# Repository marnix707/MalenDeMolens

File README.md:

# MalenDeMolens
Sensor om bedrijfstoestand van oude poldermolens te bepalen en door te sturen over het LoRaWAN netwerk.

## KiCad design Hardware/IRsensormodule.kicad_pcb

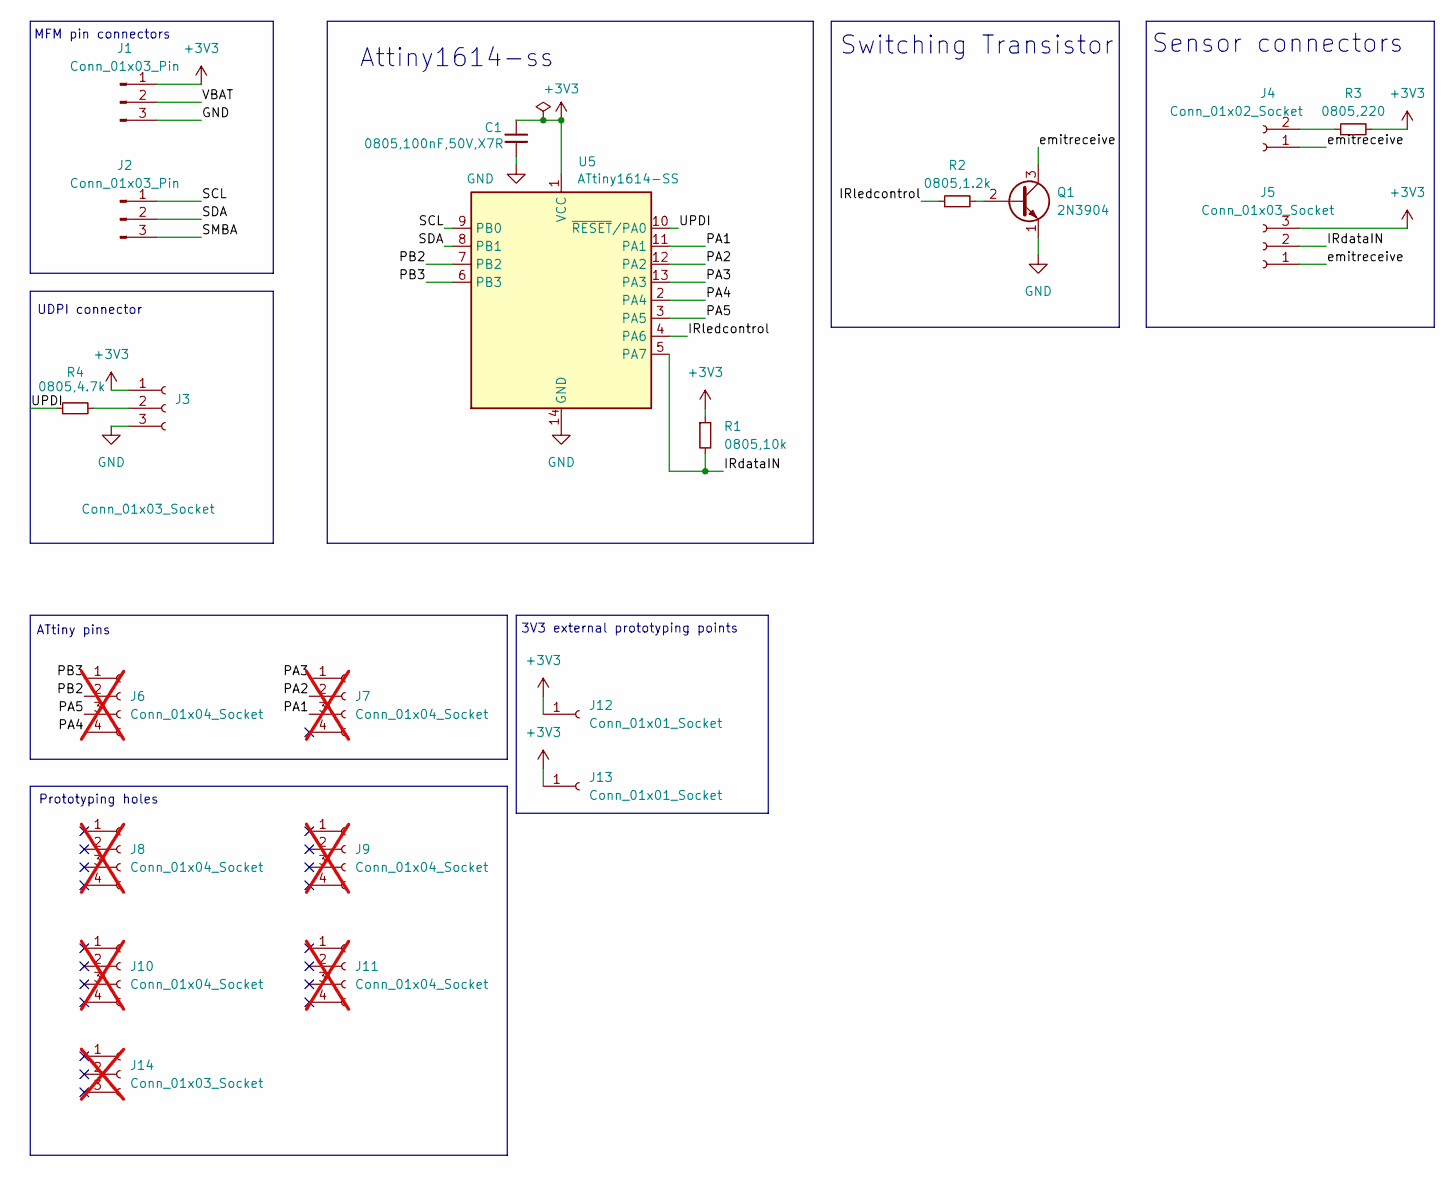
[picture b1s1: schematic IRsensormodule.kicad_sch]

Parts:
C1: 0805,100nF,50V,X7R; C_0805_2012Metric; MFGPN CC0805KRX7R9BB104; LCSC C49678
J1, J2: Conn_01x03_Pin; PinHeader_1x03_P2.54mm_Vertical
J3: Conn_01x03_Socket; PinSocket_1x03_P2.54mm_Vertical
J4: Conn_01x02_Socket; JST_GH_BM02B-GHS-TBT_1x02-1MP_P1.25mm_Vertical
J5: Conn_01x03_Socket; JST_GH_BM03B-GHS-TBT_1x03-1MP_P1.25mm_Vertical
J6, J7, J8, J9, J10, J11: Conn_01x04_Socket; PinHeader_1x04_P2.54mm_Vertical; not fitted
J12, J13: Conn_01x01_Socket; PinSocket_1x01_P2.54mm_Vertical
J14: Conn_01x03_Socket; PinSocket_1x03_P2.54mm_Vertical; not fitted
Q1: 2N3904; TO-92_Inline
R1: 0805,10k; R_0805_2012Metric; MFGPN 0805W8F1002T5E; LCSC C17414
R2: 0805,1.2k; R_0805_2012Metric; MFGPN 0805W8F1201T5E; LCSC C17379
R3: 0805,220; R_0805_2012Metric; MFGPN 0805W8F2200T5E; LCSC C17557
R4: 0805,4.7k; R_0805_2012Metric; MFGPN 0805W8F4701T5E; LCSC C17673
U5: ATtiny1614-SS; SOIC-14_3.9x8.7mm_P1.27mm

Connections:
+3V3: C1.1, J1.1, J3.1, J5.3, J12.1, J13.1, R1.1, R3.2, U5.1 (VCC)
/IRdataIN: J5.2, R1.2, U5.5 (PA7)
/IRledcontrol: R2.1, U5.4 (PA6)
/PA1: J7.3, U5.11 (PA1)
/PA2: J7.2, U5.12 (PA2)
/PA3: J7.1, U5.13 (PA3)
/PA4: J6.4, U5.2 (PA4)
/PA5: J6.3, U5.3 (PA5)
/PB2: J6.2, U5.7 (PB2)
/PB3: J6.1, U5.6 (PB3)
/SCL: J2.1, U5.9 (PB0)
/SDA: J2.2, U5.8 (PB1)
/SMBA: J2.3
/UPDI: R4.1, U5.10 (~RESET/PA0)
/VBAT: J1.2
/emitreceive: J4.1, J5.1, Q1.3 (C)
GND: C1.2, J1.3, J3.3, Q1.1 (E), U5.14 (GND)
unnamed: J3.2, R4.2
unnamed: J4.2, R3.1
unnamed: Q1.2 (B), R2.2

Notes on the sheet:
Prototyping holes
Sensor connectors
MFM pin connectors
Attiny1614-ss
UDPI connector
3V3 external prototyping points
Switching Transistor
ATtiny pins

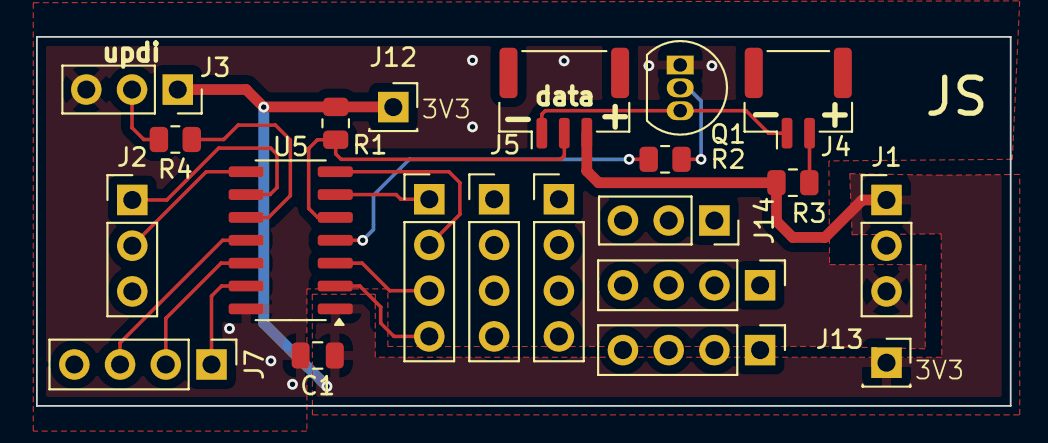
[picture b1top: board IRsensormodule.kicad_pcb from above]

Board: 2 copper layers, 54.1 x 20.5 mm, 21 parts (0 on the bottom side), 18 nets.

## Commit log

2026-01-27 Add I2C sensor module for gemaalrotatie
2026-01-27 Rename sensor_module_i2c to sensor_module_i2c.ino
2026-01-27 added folders
2026-01-27 eddited
2026-02-11 Correct spelling of 'MultiFlexMeter' to 'Multiflexmeter'
2026-03-09 Hardware files sensor module
2026-03-09 Update sensor_module_i2c.ino
    Debounce timer toegevoegd. Standaard op 20ms tussen pulsen gezet
